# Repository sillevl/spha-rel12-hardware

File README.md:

# Twelve-channel relay module

SPHA twelve-channel relay/light-output module.

## Design files

- `relay-module-light.kicad_pro` — KiCad project
- `relay-module-light.kicad_sch` — top-level schematic
- `relay-module-light.kicad_pcb` — PCB layout
- Additional `.kicad_sch` files — hierarchical schematic sheets
- `models/` — project-specific 3D and mechanical models

## Working with the project

Open the `.kicad_pro` file in KiCad. The design includes files originating from an older KiCad workflow; review schematic links, footprints, design rules, zones, and manufacturing outputs after any conversion or upgrade.

KiCad source files and project-specific libraries are the source of truth. Generated BOM, Gerber, assembly, and fabrication-house outputs are excluded from the repository; regenerate and verify them before manufacturing.

## Repository notes

Temporary KiCad state, locks, autosaves, and backup directories are excluded by `.gitignore`. Board revision, tested KiCad version, manufacturing revision, and hardware/firmware compatibility still need to be recorded when provenance is confirmed.

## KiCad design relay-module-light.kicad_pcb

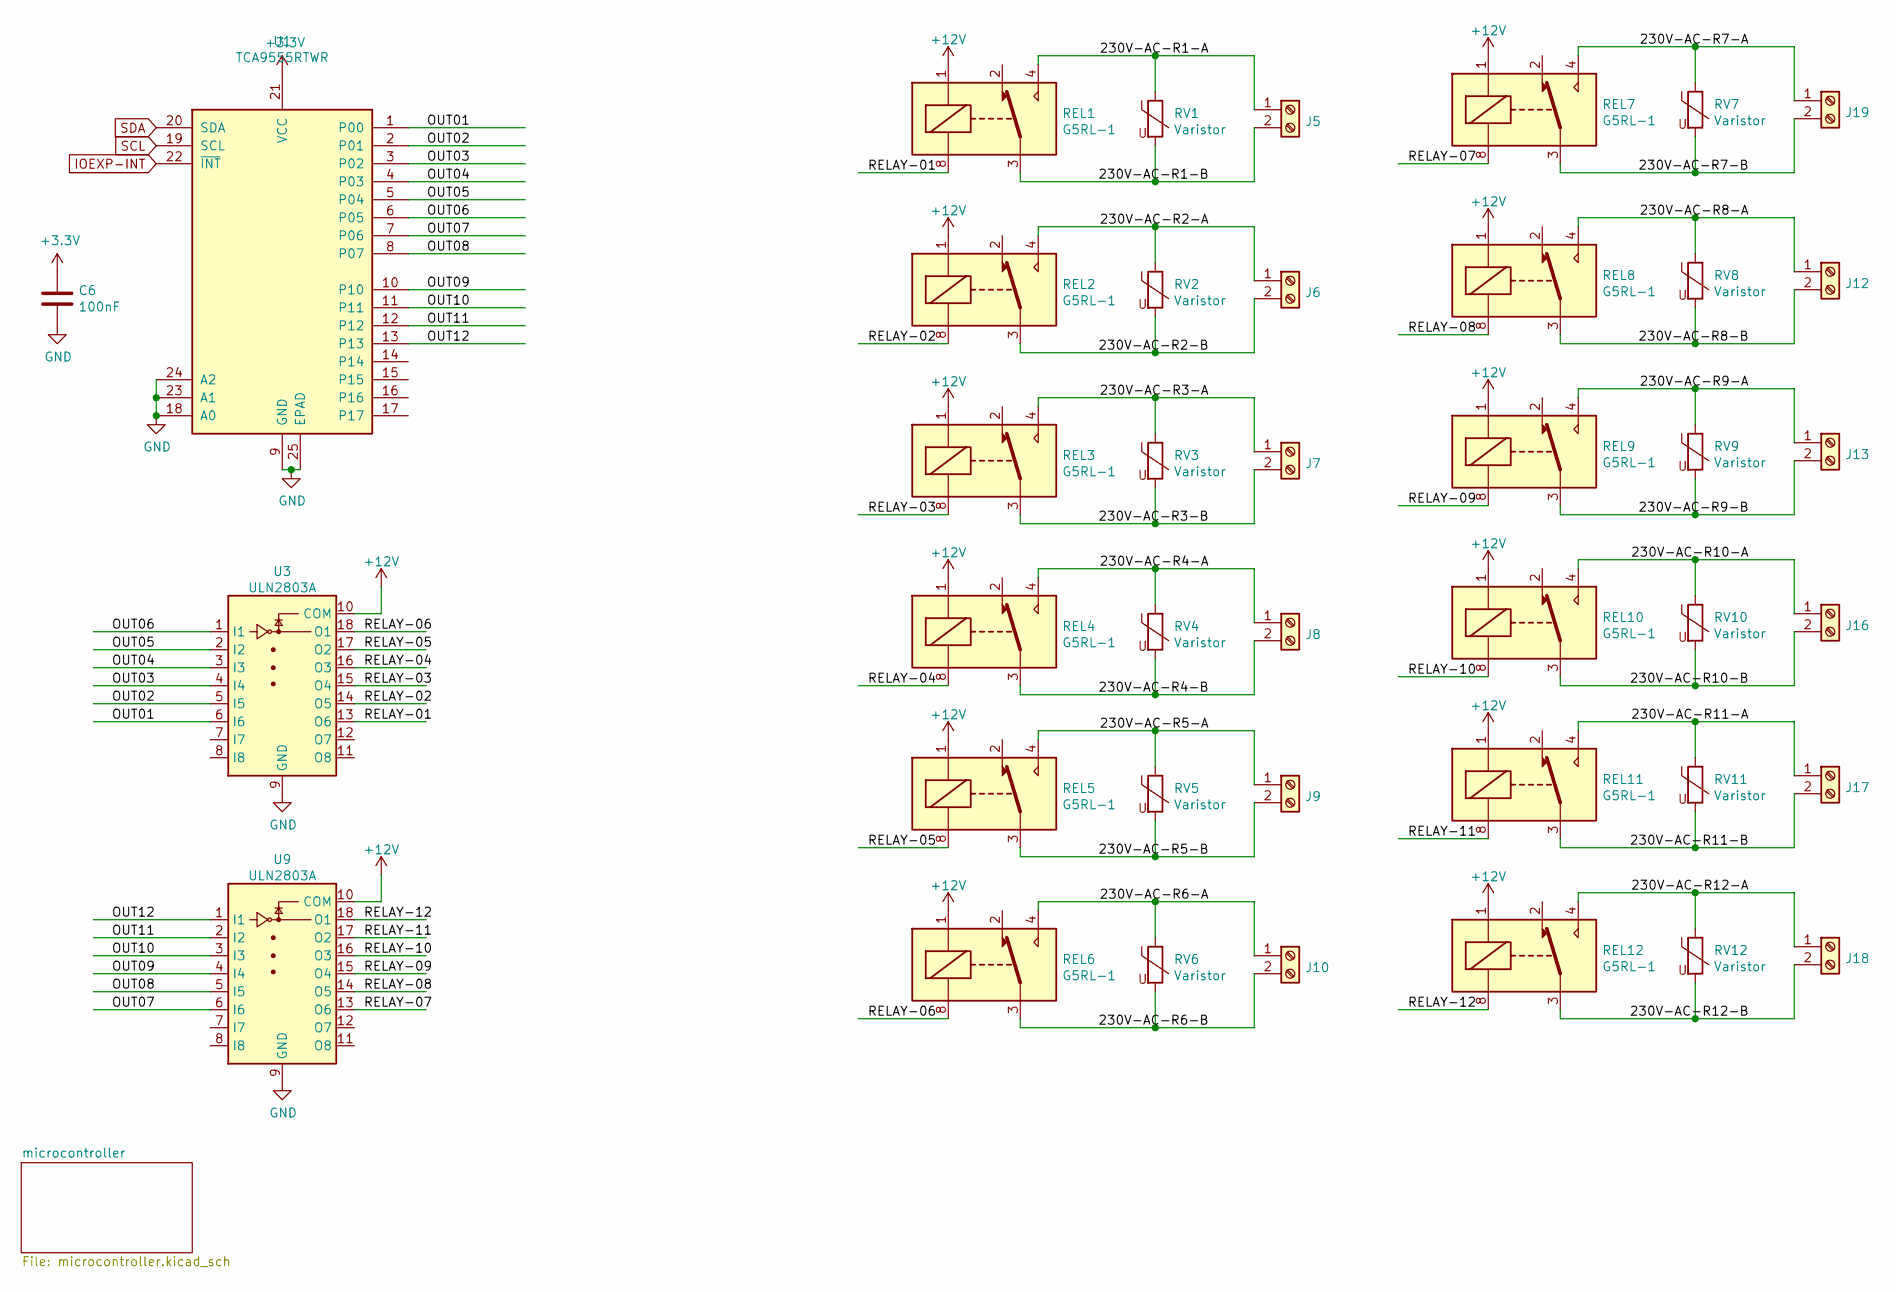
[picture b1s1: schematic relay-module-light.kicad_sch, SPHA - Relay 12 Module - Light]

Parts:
C6: 100nF; C_0603_1608Metric_Pad1.05x0.95mm_HandSolder
J5, J6, J7, J8, J9, J10, J12, J13, J16, J17, J18, J19: Screw_Terminal_01x02; TerminalBlock_MetzConnect_Type175_RT02702HBLC_1x02_P7.50mm_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
REL1, REL2, REL3, REL4, REL5, REL6, REL7, REL8, REL9, REL10, REL11, REL12: G5RL-1; Relay_DPDT_Omron_G2RL
RV1, RV2, RV3, RV4, RV5, RV6, RV7, RV8, RV9, RV10, RV11, RV12: Varistor; RV_Disc_D7mm_W4mm_P5mm
U1: TCA9555RTWR; WQFN-24-1EP_4x4mm_P0.5mm_EP2.45x2.45mm
U3, U9: ULN2803A; SOP-18_7x12.5mm_P1.27mm

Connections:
+12V: REL1.1, REL2.1, REL3.1, REL4.1, REL5.1, REL6.1, REL7.1, REL8.1, REL9.1, REL10.1, REL11.1, REL12.1, U3.10 (COM), U9.10 (COM); also elsewhere on the board
/230V-AC-R1-A: J5.1, REL1.4, REL1.5, RV1.1
/230V-AC-R1-B: J5.2, REL1.3, REL1.6, RV1.2
/230V-AC-R2-A: J6.1, REL2.4, REL2.5, RV2.1
/230V-AC-R2-B: J6.2, REL2.3, REL2.6, RV2.2
/230V-AC-R3-A: J7.1, REL3.4, REL3.5, RV3.1
/230V-AC-R3-B: J7.2, REL3.3, REL3.6, RV3.2
/230V-AC-R4-A: J8.1, REL4.4, REL4.5, RV4.1
/230V-AC-R4-B: J8.2, REL4.3, REL4.6, RV4.2
/230V-AC-R5-A: J9.1, REL5.4, REL5.5, RV5.1
/230V-AC-R5-B: J9.2, REL5.3, REL5.6, RV5.2
/230V-AC-R6-A: J10.1, REL6.4, REL6.5, RV6.1
/230V-AC-R6-B: J10.2, REL6.3, REL6.6, RV6.2
/230V-AC-R7-A: J19.1, REL7.4, REL7.5, RV7.1
/230V-AC-R7-B: J19.2, REL7.3, REL7.6, RV7.2
/230V-AC-R8-A: J12.1, REL8.4, REL8.5, RV8.1
/230V-AC-R8-B: J12.2, REL8.3, REL8.6, RV8.2
/230V-AC-R9-A: J13.1, REL9.4, REL9.5, RV9.1
/230V-AC-R9-B: J13.2, REL9.3, REL9.6, RV9.2
/230V-AC-R10-A: J16.1, REL10.4, REL10.5, RV10.1
/230V-AC-R10-B: J16.2, REL10.3, REL10.6, RV10.2
/230V-AC-R11-A: J17.1, REL11.4, REL11.5, RV11.1
/230V-AC-R11-B: J17.2, REL11.3, REL11.6, RV11.2
/230V-AC-R12-A: J18.1, REL12.4, REL12.5, RV12.1
/230V-AC-R12-B: J18.2, REL12.3, REL12.6, RV12.2
/OUT01: U1.1 (P00), U3.6 (I6)
/OUT02: U1.2 (P01), U3.5 (I5)
/OUT03: U1.3 (P02), U3.4 (I4)
/OUT04: U1.4 (P03), U3.3 (I3)
/OUT05: U1.5 (P04), U3.2 (I2)
/OUT06: U1.6 (P05), U3.1 (I1)
/OUT07: U1.7 (P06), U9.6 (I6)
/OUT08: U1.8 (P07), U9.5 (I5)
/OUT09: U1.10, U9.4 (I4)
/OUT10: U1.11, U9.3 (I3)
/OUT11: U1.12, U9.2 (I2)
/OUT12: U1.13, U9.1 (I1)
/RELAY-01: REL1.8, U3.13 (O6)
/RELAY-02: REL2.8, U3.14 (O5)
/RELAY-03: REL3.8, U3.15 (O4)
/RELAY-04: REL4.8, U3.16 (O3)
/RELAY-05: REL5.8, U3.17 (O2)
/RELAY-06: REL6.8, U3.18 (O1)
/RELAY-07: REL7.8, U9.13 (O6)
/RELAY-08: REL8.8, U9.14 (O5)
/RELAY-09: REL9.8, U9.15 (O4)
/RELAY-10: REL10.8, U9.16 (O3)
/RELAY-11: REL11.8, U9.17 (O2)
/RELAY-12: REL12.8, U9.18 (O1)
IOEXP-INT: U1.22 (~INT); also elsewhere on the board
unnamed: REL1.2, REL1.7
unnamed: REL2.2, REL2.7
unnamed: REL3.2, REL3.7
unnamed: REL4.2, REL4.7
unnamed: REL5.2, REL5.7
unnamed: REL6.2, REL6.7
unnamed: REL7.2, REL7.7
unnamed: REL8.2, REL8.7
unnamed: REL9.2, REL9.7
unnamed: REL10.2, REL10.7
unnamed: REL11.2, REL11.7
unnamed: REL12.2, REL12.7
SCL: U1.19 (SCL); also elsewhere on the board
SDA: U1.20 (SDA); also elsewhere on the board

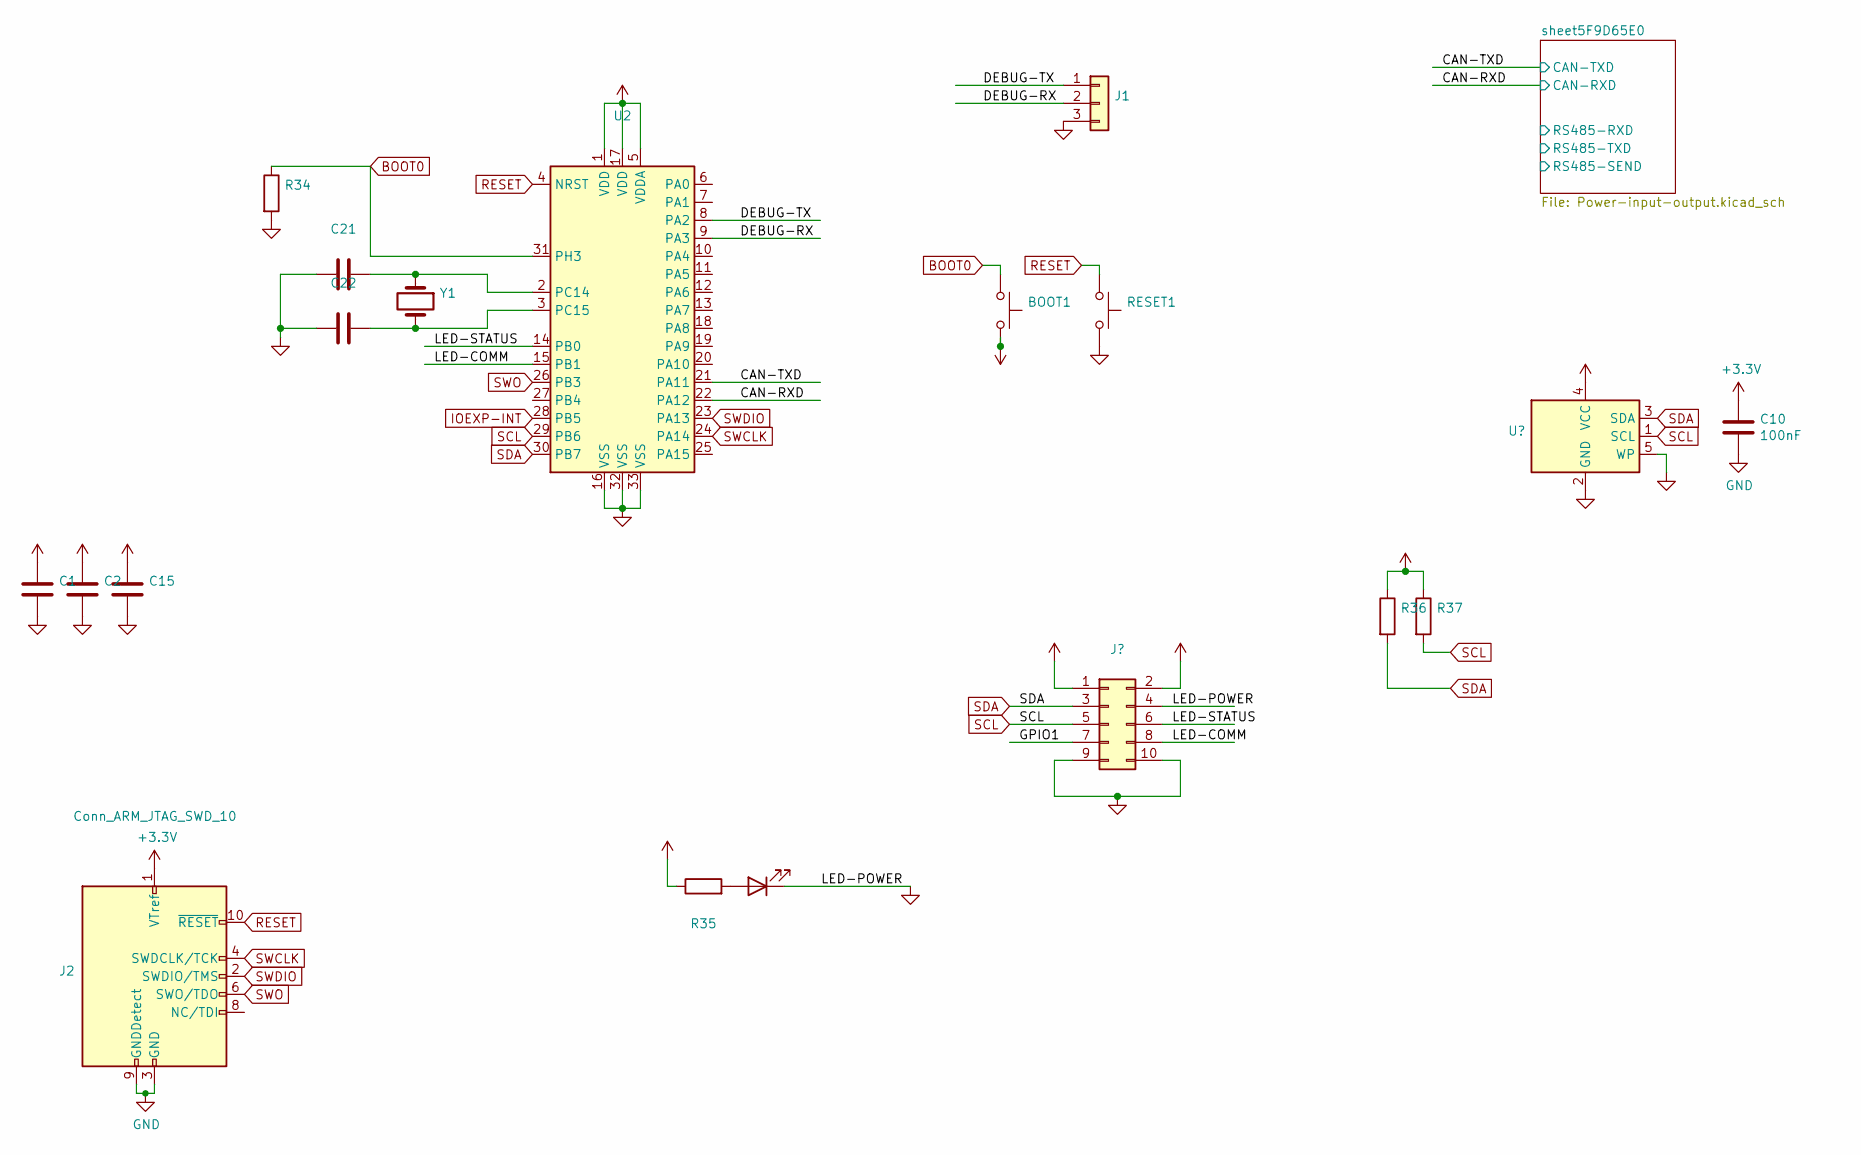
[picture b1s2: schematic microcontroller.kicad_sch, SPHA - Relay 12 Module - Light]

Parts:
BOOT1: (no value)
C1, C2, C15, C21, C22: (no value)
C10: 100nF; C_0603_1608Metric_Pad1.05x0.95mm_HandSolder
J1: (no value)
J2: Conn_ARM_JTAG_SWD_10; PinHeader_2x05_P1.27mm_Vertical_SMD
LED1: (no value)
R34, R35, R36, R37: (no value)
RESET1: (no value)
U2: (no value)
Y1: (no value)

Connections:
/microcontroller/CAN-RXD: U2.22 (PA12); also elsewhere on the board
/microcontroller/CAN-TXD: U2.21 (PA11); also elsewhere on the board
/microcontroller/DEBUG-RX: J1.2, U2.9 (PA3)
/microcontroller/DEBUG-TX: J1.1, U2.8 (PA2)
/microcontroller/LED-COMM: U2.15 (PB1); also elsewhere on the board
/microcontroller/LED-STATUS: U2.14 (PB0); also elsewhere on the board
BOOT0: BOOT1.1, R34.1, U2.31 (PH3)
IOEXP-INT: U2.28 (PB5); also elsewhere on the board
unnamed: C21.1, U2.2 (PC14), Y1.1
unnamed: C22.1, U2.3 (PC15), Y1.2
unnamed: LED1.2 (A), R35.2
RESET: J2.10 (~RESET~), RESET1.1, U2.4 (NRST)
SCL: R37.2, U2.29 (PB6); also elsewhere on the board
SDA: R36.2, U2.30 (PB7); also elsewhere on the board
SWCLK: J2.4 (SWDCLK/TCK), U2.24 (PA14)
SWDIO: J2.2 (SWDIO/TMS), U2.23 (PA13)
SWO: J2.6 (SWO/TDO), U2.26 (PB3)

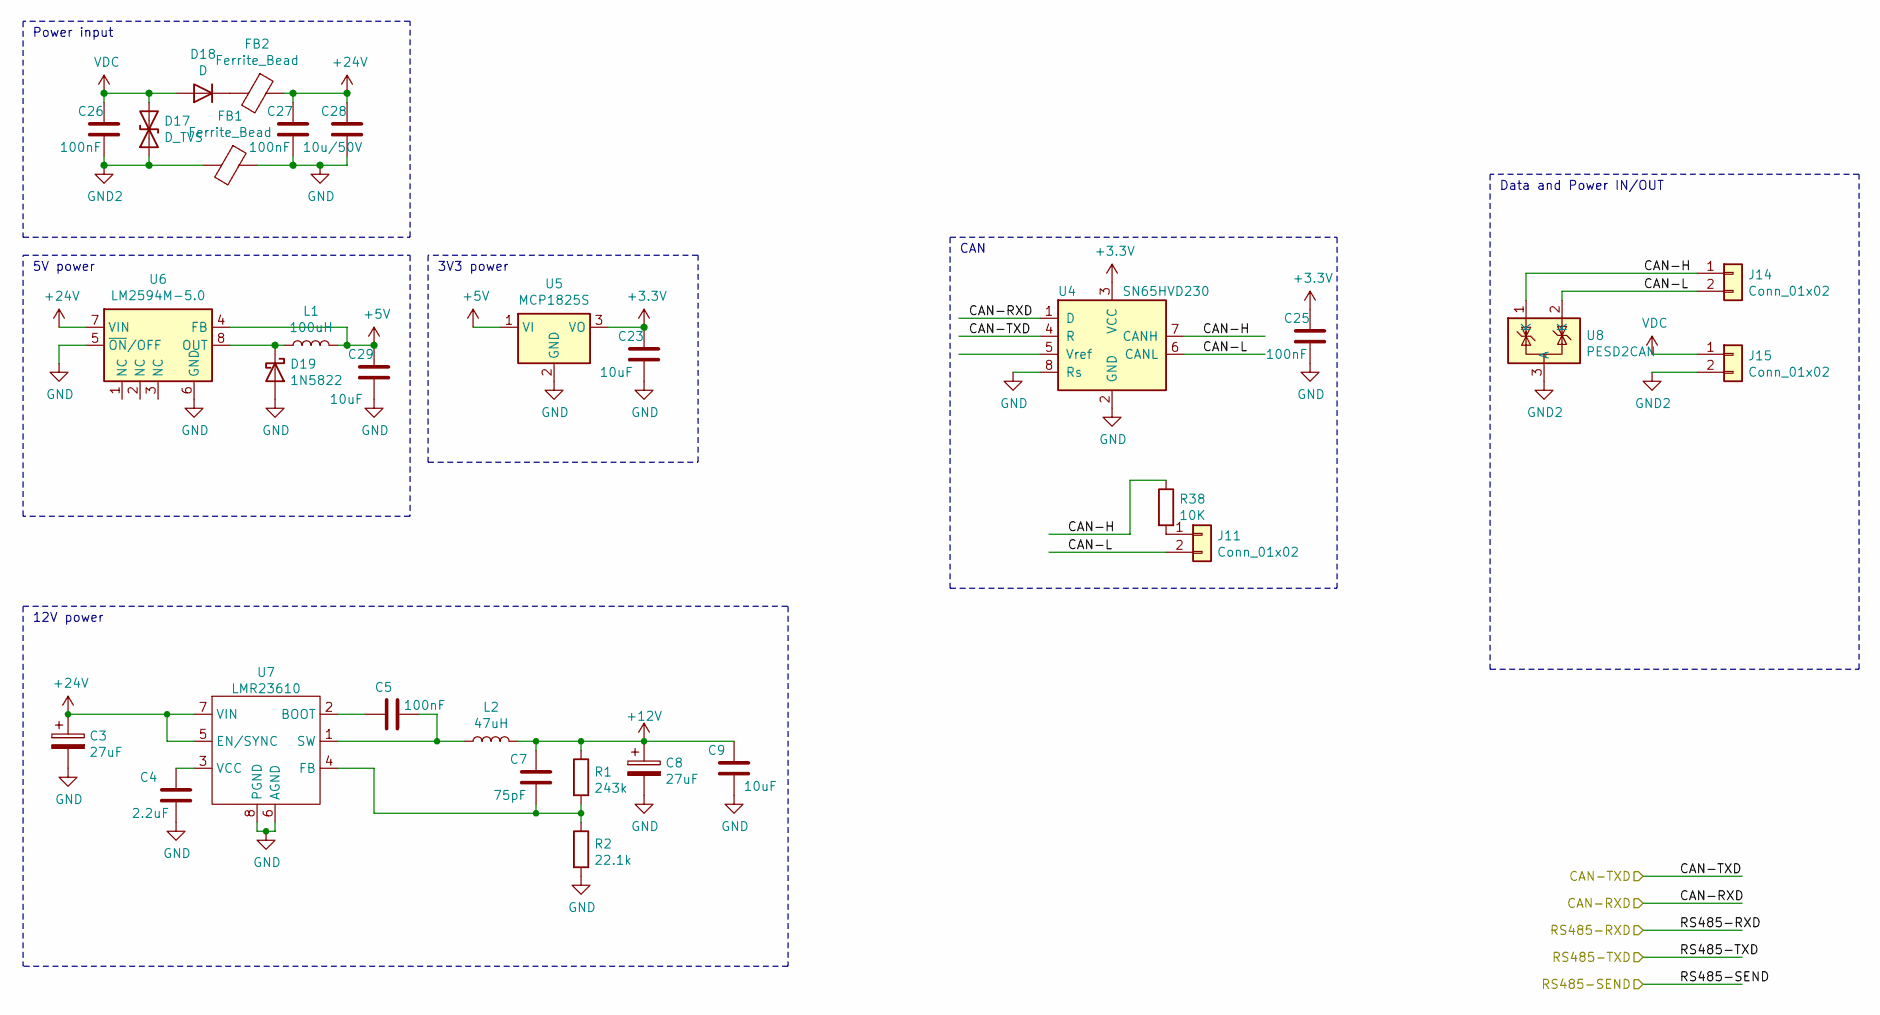
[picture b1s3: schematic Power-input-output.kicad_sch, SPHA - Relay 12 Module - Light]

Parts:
C3, C8: 27uF; CP_Elec_6.3x5.7
C4: 2.2uF; C_0603_1608Metric
C5, C25, C26, C27: 100nF; C_0603_1608Metric
C7: 75pF; C_0603_1608Metric
C9, C23, C29: 10uF; C_1206_3216Metric
C28: 10u/50V; C_1206_3216Metric
D17: D_TVS; D_SMB
D18: D; D_SMA
D19: 1N5822; D_SOD-123
FB1, FB2: Ferrite_Bead; R_0603_1608Metric
J11: Conn_01x02; PinHeader_1x02_P2.54mm_Vertical
J14, J15: Conn_01x02; TerminalBlock_bornier-2_P5.08mm
L1: 100uH; L_Wuerth_WE-PD2-Typ-MS
L2: 47uH; L_12x12mm_H8mm
R1: 243k; R_0603_1608Metric
R2: 22.1k; R_0603_1608Metric
R38: 10K; R_0603_1608Metric
U4: SN65HVD230; SOIC-8_3.9x4.9mm_P1.27mm
U5: MCP1825S; SOT-223
U6: LM2594M-5.0; SOIC-8_3.9x4.9mm_P1.27mm
U7: LMR23610; HSOIC-8
U8: PESD2CAN; SOT-23

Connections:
+5V: C29.1, L1.2, U5.1 (VI), U6.4 (FB); also elsewhere on the board
+12V: C7.2, C8.1, C9.1, L2.2, R1.1; also elsewhere on the board
+24V: C3.1, C27.1, C28.1, FB2.1, U6.7 (VIN), U7.5 (EN/SYNC), U7.7 (VIN)
/microcontroller/CAN-RXD: U4.1 (D); also elsewhere on the board
/microcontroller/CAN-TXD: U4.4 (R); also elsewhere on the board
/microcontroller/sheet5F9D65E0/CAN-H: J14.1, R38.1, U4.7 (CANH), U8.1 (K)
/microcontroller/sheet5F9D65E0/CAN-L: J11.2, J14.2, U4.6 (CANL), U8.2 (K)
GND2: C26.2, D17.1 (A1), FB1.2, J15.2, U8.3 (A)
unnamed: C4.1, U7.3 (VCC)
unnamed: C5.1, U7.2 (BOOT)
unnamed: C5.2, L2.1, U7.1 (SW)
unnamed: C7.1, R1.2, R2.1, U7.4 (FB)
unnamed: D18.1 (K), FB2.2
unnamed: D19.1 (K), L1.1, U6.8 (OUT)
unnamed: J11.1, R38.2
VDC: C26.1, D17.2 (A2), D18.2 (A), J15.1

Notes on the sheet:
12V power
3V3 power
CAN
5V power
Data and Power IN/OUT
Power input

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
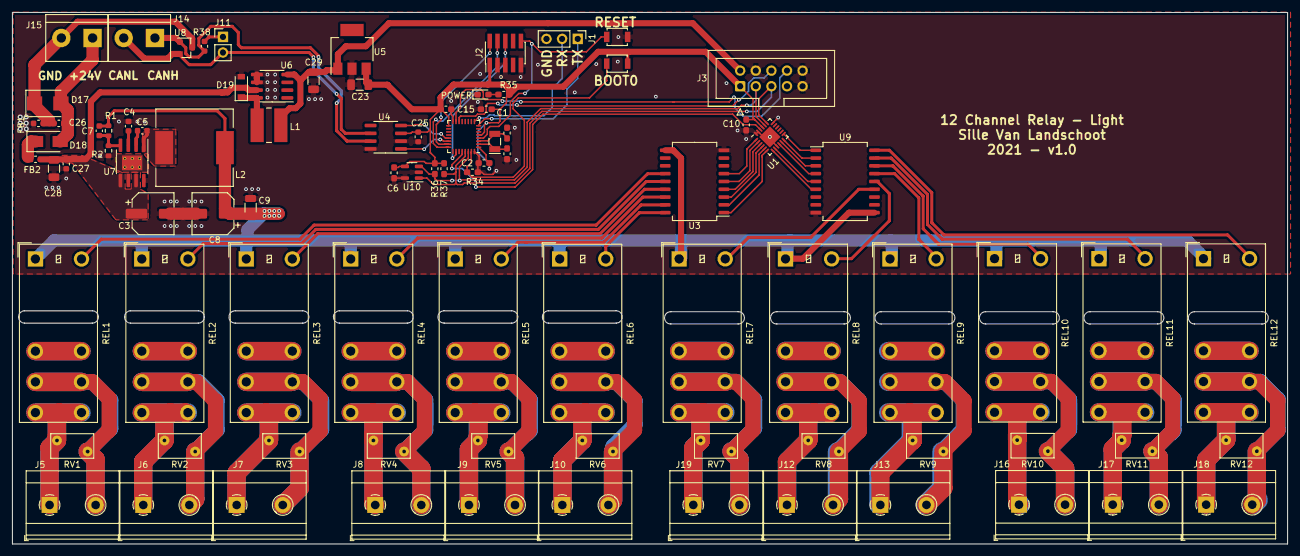
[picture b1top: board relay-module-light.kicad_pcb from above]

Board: 2 copper layers, 207.5 x 86.5 mm, 89 parts (0 on the bottom side), 93 nets.

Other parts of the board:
J3: Conn_02x05_Odd_Even; IDC-Header_2x05_P2.54mm_Vertical
U10: AT24CS32-STUM; SOT-23-5

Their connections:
+5V: J3.2; also elsewhere on the board
/microcontroller/LED-COMM: J3.8; also elsewhere on the board
/microcontroller/LED-STATUS: J3.6; also elsewhere on the board
SCL: J3.5, U10.1 (SCL); also elsewhere on the board
SDA: J3.3, U10.3 (SDA); also elsewhere on the board
